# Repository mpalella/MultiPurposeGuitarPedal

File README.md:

# MultiPurposeGuitarPedal
Files that go along with my digital guitar pedal project

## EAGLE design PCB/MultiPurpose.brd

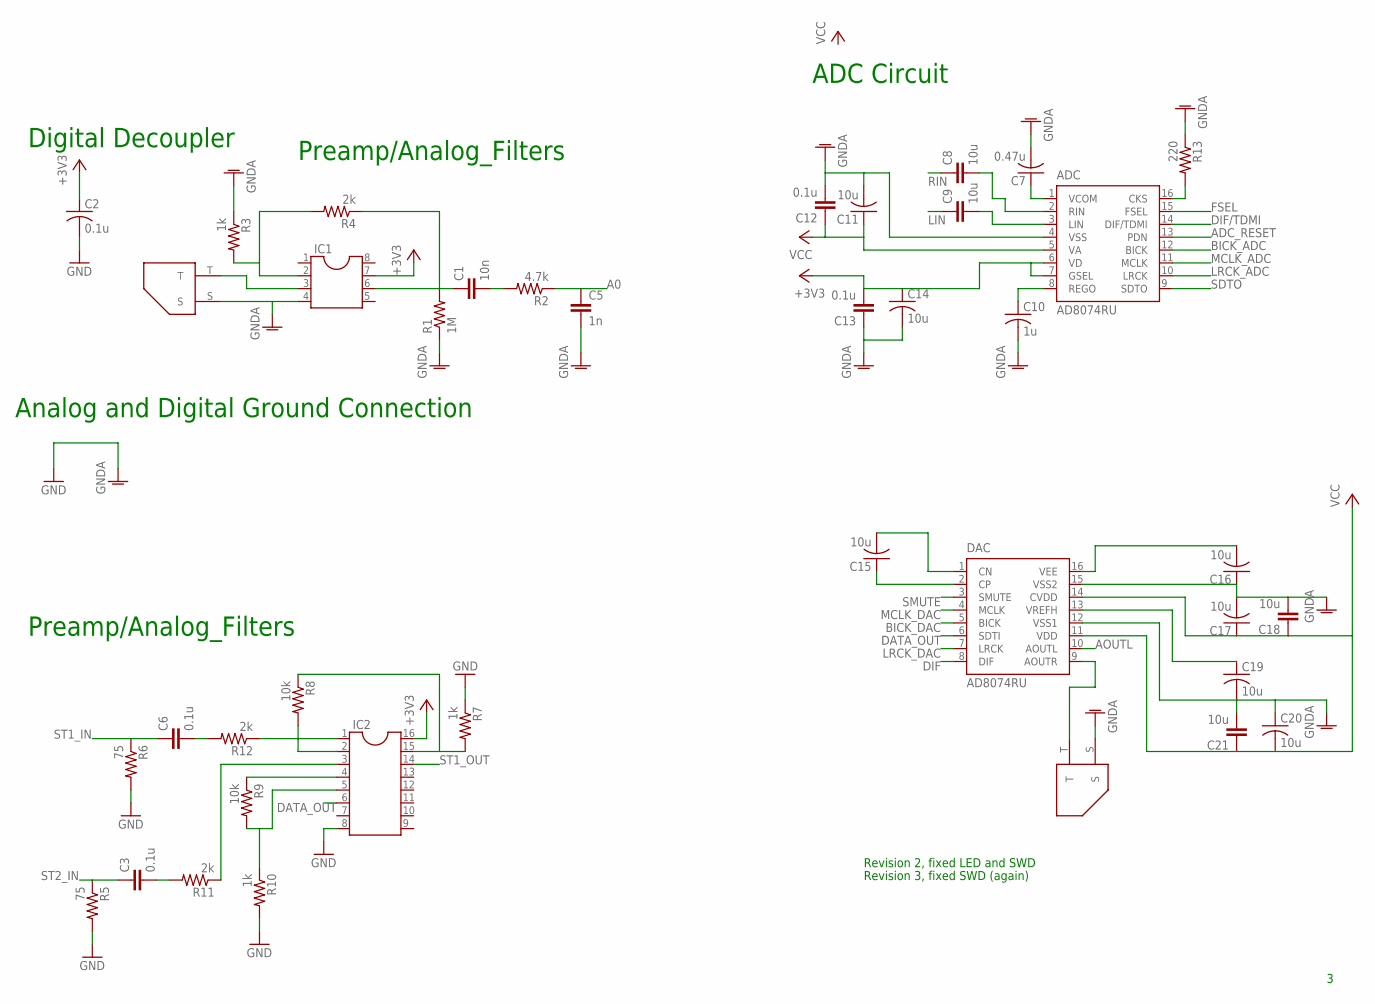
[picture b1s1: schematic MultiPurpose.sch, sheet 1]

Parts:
ADC: AD8074RU; TSSOP16
C1: 10n; C2.5-2
C2: 0.1u; C050-024X044
C3, C6, C12, C13: 0.1u; C2.5-2
C5: 1n; C2.5-2
C7: 0.47u; C050-024X044
C8, C9, C18, C21: 10u; C2.5-2
C10: 1u; C050-024X044
C11, C14, C15, C16, C17, C19, C20: 10u; C050-024X044
DAC: AD8074RU; TSSOP16
IC1: DIL8S; SOCKET-08
IC2: DIL16S; SOCKET-16
R1: 1M; 0207/10
R2: 4.7k; 0207/10
R3, R7, R10: 1k; 0207/10
R4, R11, R12: 2k; 0207/10
R5, R6: 75; 0207/10
R8, R9: 10k; 0207/10
R13: 220; 0207/10
U$1, U$2: TS_JACK; MONO_1

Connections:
+3V3: ADC.6 (VD), ADC.7 (GSEL), C13.2, C14.1, IC1.7, IC2.16; also elsewhere on the board
+5V5: C2.1
A0: C5.1, R2.1
ADC_RESET: ADC.13 (PDN)
AOUTL: DAC.10 (AOUTL)
AOUTR: DAC.9 (AOUTR), U$2.T
BICK_ADC: ADC.12 (BICK)
BICK_DAC: DAC.5 (BICK)
DATA_OUT: DAC.6 (SDTI), IC2.5, IC2.6, R9.2, R10.1
DIF: DAC.8 (DIF)
DIF/TDMI: ADC.14 (DIF/TDMI)
FSEL: ADC.15 (FSEL)
GND: C2.2, IC2.8, R5.2, R6.2, R7.1, R10.2; also elsewhere on the board
GNDA: ADC.4 (VSS), C5.2, C7.2, C10.2, C11.2, C12.2, C13.1, C14.2, C16.1, C17.2, C18.2, C19.2, C20.1, C21.2, DAC.12 (VSS1), DAC.15 (VSS2), IC1.4, R1.1, R3.1, R13.1, U$1.S, U$2.S
LIN: C9.1
LRCK_ADC: ADC.10 (LRCK)
LRCK_DAC: DAC.7 (LRCK)
MCLK_ADC: ADC.11 (MCLK)
MCLK_DAC: DAC.4 (MCLK)
unnamed: ADC.1 (VCOM), C7.1
unnamed: IC1.3, U$1.T
unnamed: IC1.2, R3.2, R4.2
unnamed: C6.2, R12.2
unnamed: C1.1, IC1.6, R1.2, R4.1
unnamed: C1.2, R2.2
unnamed: IC2.1, R12.1
unnamed: IC2.2, R8.2
unnamed: IC2.15, R7.2, R8.1
unnamed: C3.2, R11.2
unnamed: IC2.3, R11.1
unnamed: IC2.4, R9.1
unnamed: ADC.3 (LIN), C9.2
unnamed: ADC.2 (RIN), C8.2
unnamed: C16.2, DAC.16 (VEE)
unnamed: ADC.8 (REGO), C10.1
unnamed: ADC.16 (CKS), R13.2
unnamed: C15.2, DAC.1 (CN)
unnamed: C15.1, DAC.2 (CP)
unnamed: C19.1, DAC.13 (VREFH)
RIN: C8.1
SDTO: ADC.9 (SDTO)
SMUTE: DAC.3 (SMUTE)
ST1_IN: C6.1, R6.1
ST1_OUT: IC2.14
ST2_IN: C3.1, R5.1
VCC: ADC.5 (VA), C11.1, C12.1, C17.1, C18.1, C20.2, C21.1, DAC.11 (VDD), DAC.14 (CVDD)

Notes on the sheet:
Revision 2, fixed LED and SWD
Revision 3, fixed SWD (again)
Digital Decoupler
Preamp/Analog_Filters
Analog and Digital Ground Connection
ADC Circuit

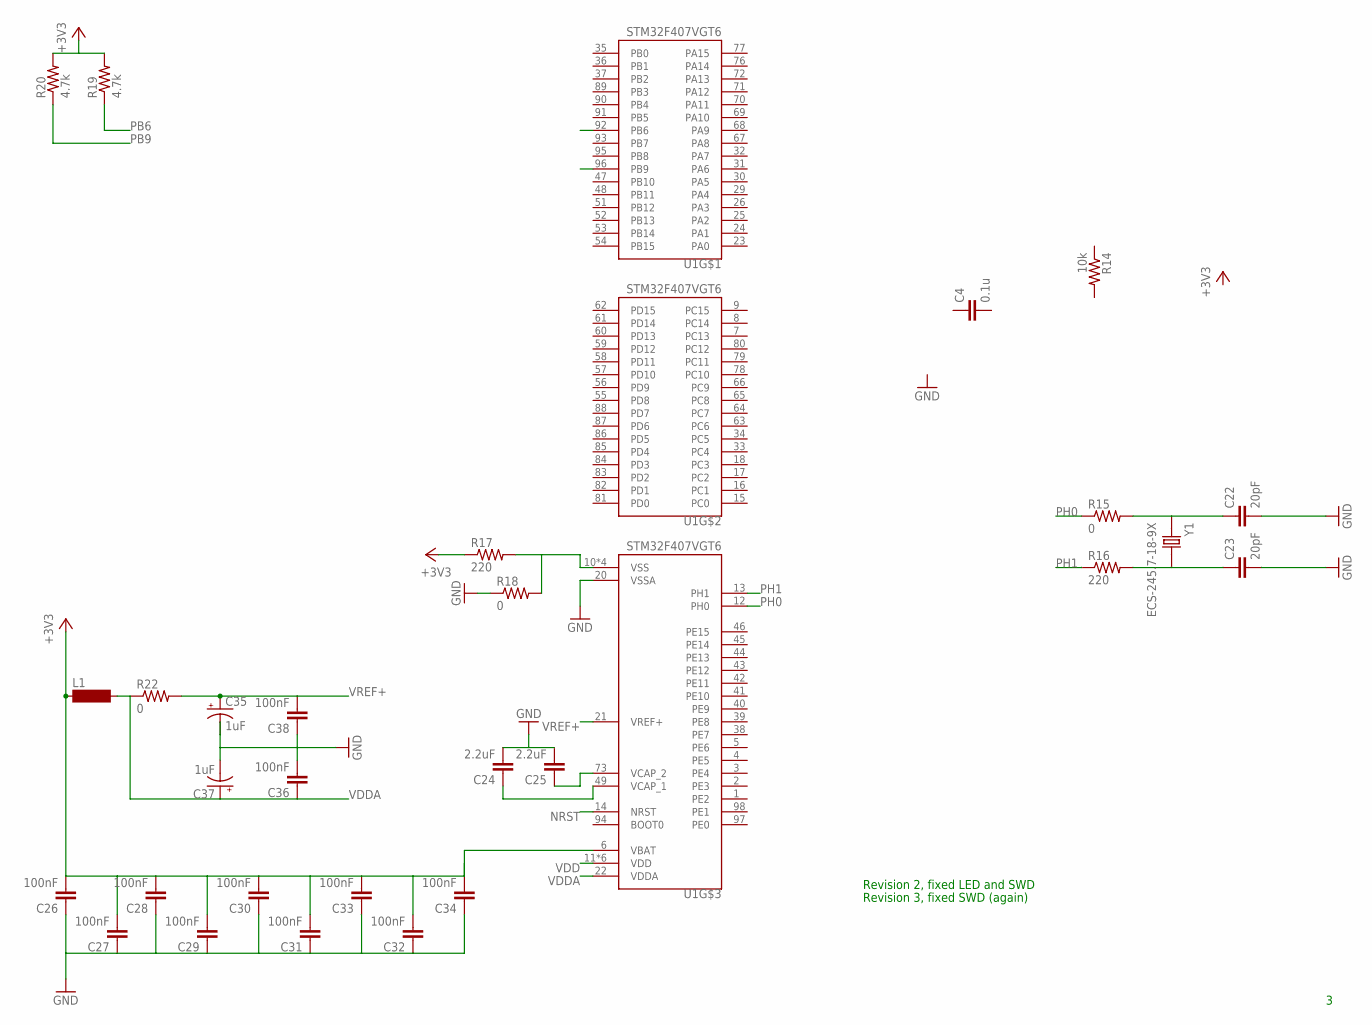
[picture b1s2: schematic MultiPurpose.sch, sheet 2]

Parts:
C4: 0.1u; C2.5-2
C22, C23: 20pF; C2.5-2
C24, C25: 2.2uF; C2.5-2
C26, C27, C28, C29, C30, C31, C32, C33, C34, C36, C38: 100nF; C2.5-2
C35, C37: 1uF; 139CLL-3R
L1: BS75
R14: 10k; 0207/10
R15, R18, R22: 0; 0207/10
R16, R17: 220; 0207/10
R19, R20: 4.7k; 0207/10
U1: STM32F407VGT6; QFP50P1600X1600X160-100N
Y1: ECS-245.7-18-9X; XTAL_ECS-245.7-18-9X

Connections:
+3V3: C26.2, C27.2, C28.2, C29.2, C30.2, C31.2, C32.2, C33.2, C34.2, L1.1, R17.1, R19.2, R20.2, U1.6 (VBAT); also elsewhere on the board
GND: C22.2, C23.2, C24.2, C25.2, C26.1, C27.1, C28.1, C29.1, C30.1, C31.1, C32.1, C33.1, C34.1, C35.-, C37.-, R18.1, U1.20 (VSSA); also elsewhere on the board
unnamed: C23.1, R16.2, Y1.2
unnamed: C22.1, R15.2, Y1.1
unnamed: R17.2, R18.2, U1.10 (VSS), U1.27 (VSS), U1.74 (VSS), U1.99 (VSS)
unnamed: C24.1, U1.49 (VCAP_1)
unnamed: C25.1, U1.73 (VCAP_2)
unnamed: C36.2, C38.1
NRST: U1.14 (NRST)
PB6: R19.1, U1.92 (PB6)
PB9: R20.1, U1.96 (PB9)
PH0: R15.1, U1.12 (PH0)
PH1: R16.1, U1.13 (PH1)
VDD: U1.11 (VDD), U1.19 (VDD), U1.28 (VDD), U1.50 (VDD), U1.75 (VDD), U1.100 (VDD)
VDDA: C36.1, C37.+, L1.2, R22.1, U1.22 (VDDA)
VREF+: C35.+, C38.2, R22.2, U1.21 (VREF+)

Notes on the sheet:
Revision 2, fixed LED and SWD
Revision 3, fixed SWD (again)

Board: 2 copper layers, 68 parts (0 on the bottom side), 42 nets, no tracks yet.

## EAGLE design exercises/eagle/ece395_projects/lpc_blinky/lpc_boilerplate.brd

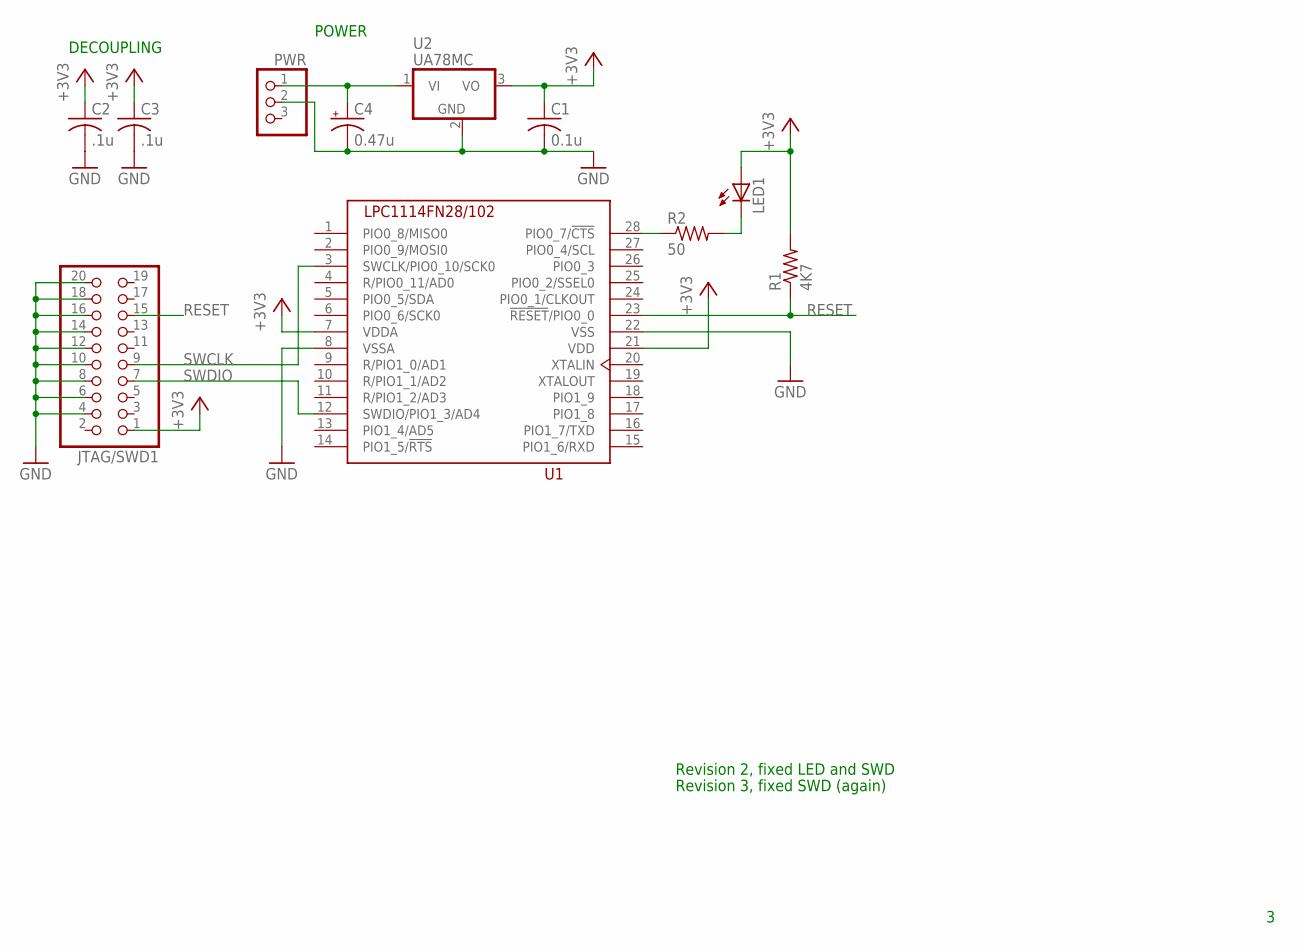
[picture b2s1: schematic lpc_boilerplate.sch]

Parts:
C1: 0.1u; C050-024X044
C2, C3: .1u; C050-024X044
C4: 0.47u; E2-5
JTAG/SWD1: PINHD-2X10; 2X10
LED1: LED10MM
PWR: PINHD-1X3; 1X03
R1: 4K7; 0207/10
R2: 50; 0207/10
U1: LPC1114FN28/102; DIL28-6
U2: UA78MC; TO220V

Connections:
+3V3: C1.1, C2.1, C3.1, JTAG/SWD1.1, LED1.A, R1.2, U1.7 (VDDA), U1.21 (VDD), U2.3 (VO)
GND: C1.2, C2.2, C3.2, C4.-, JTAG/SWD1.4, JTAG/SWD1.6, JTAG/SWD1.8, JTAG/SWD1.10, JTAG/SWD1.12, JTAG/SWD1.14, JTAG/SWD1.16, JTAG/SWD1.18, JTAG/SWD1.20, PWR.2, U1.8 (VSSA), U1.22 (VSS), U2.2 (GND)
unnamed: LED1.K (C), R2.2
unnamed: C4.+, PWR.1, U2.1 (VI)
unnamed: R2.1, U1.28 (PIO0_7/!CTS)
RESET: JTAG/SWD1.15, R1.1, U1.23 (!RESET!/PIO0_0)
SWCLK: JTAG/SWD1.9, U1.3 (SWCLK/PIO0_10/SCK0)
SWDIO: JTAG/SWD1.7, U1.12 (SWDIO/PIO1_3/AD4)

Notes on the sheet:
POWER
DECOUPLING
Revision 2, fixed LED and SWD
Revision 3, fixed SWD (again)

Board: 2 copper layers, 11 parts (0 on the bottom side), 8 nets, no tracks yet.

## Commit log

2019-11-10 Add files via upload
    committing datasheets folder
2019-11-10 Add files via upload
    Blinky Example Work
2019-11-10 adding STM C code files
2019-11-10 added Research Folder
2019-11-10 added HAL Driver Document
2019-11-18 updating workspace with I2S program file
2019-11-22 updating workspace with code that inputs/outputs data correctly from adc and dac
